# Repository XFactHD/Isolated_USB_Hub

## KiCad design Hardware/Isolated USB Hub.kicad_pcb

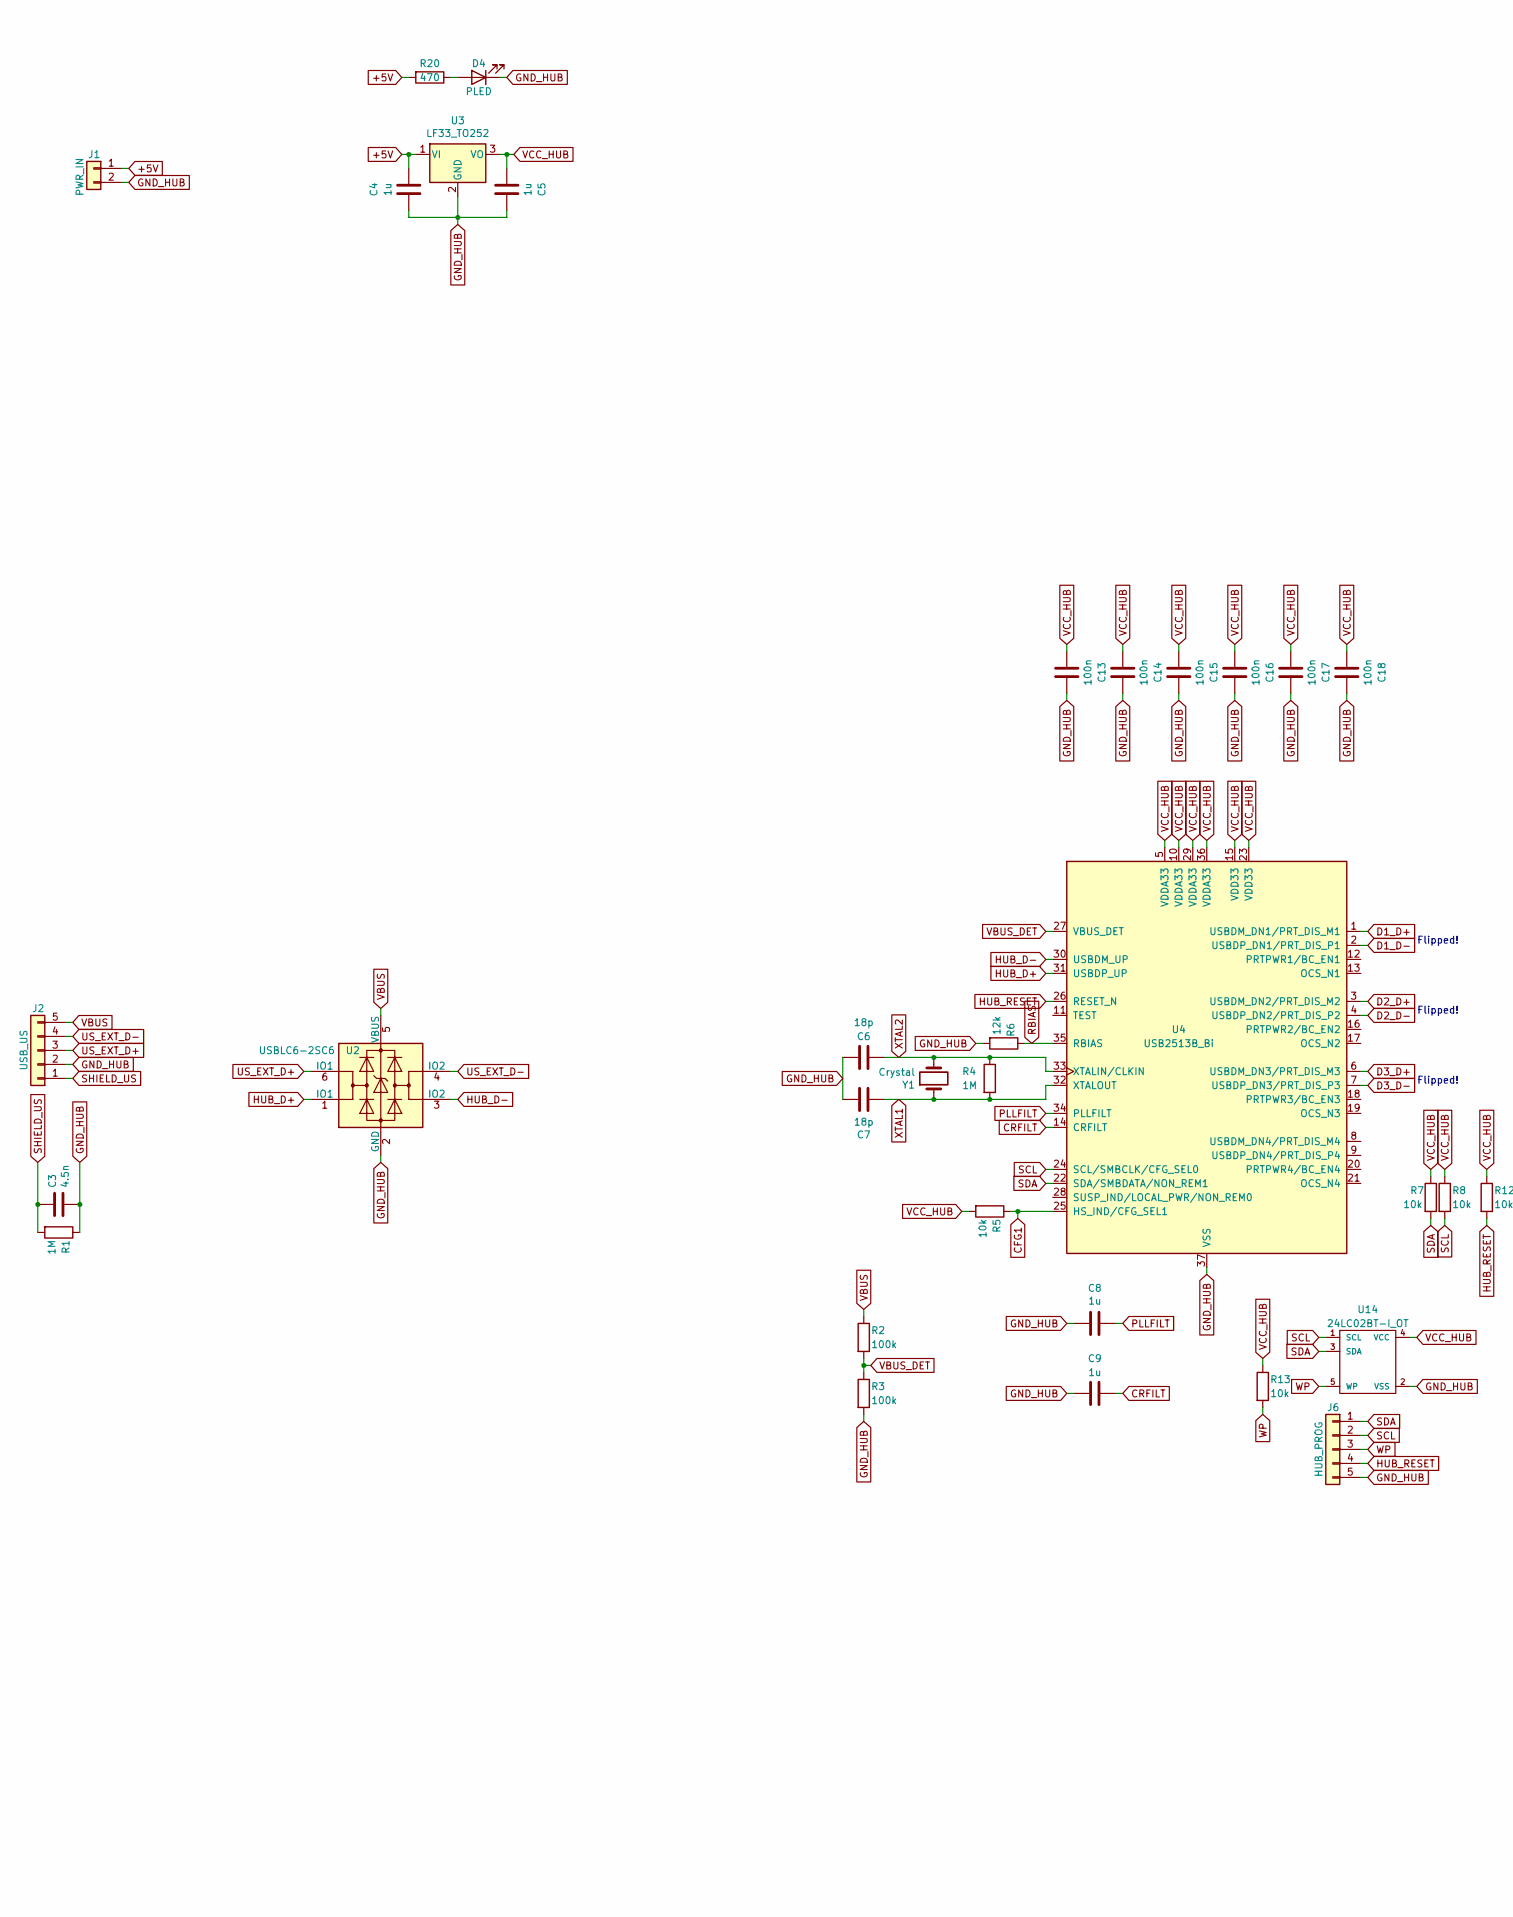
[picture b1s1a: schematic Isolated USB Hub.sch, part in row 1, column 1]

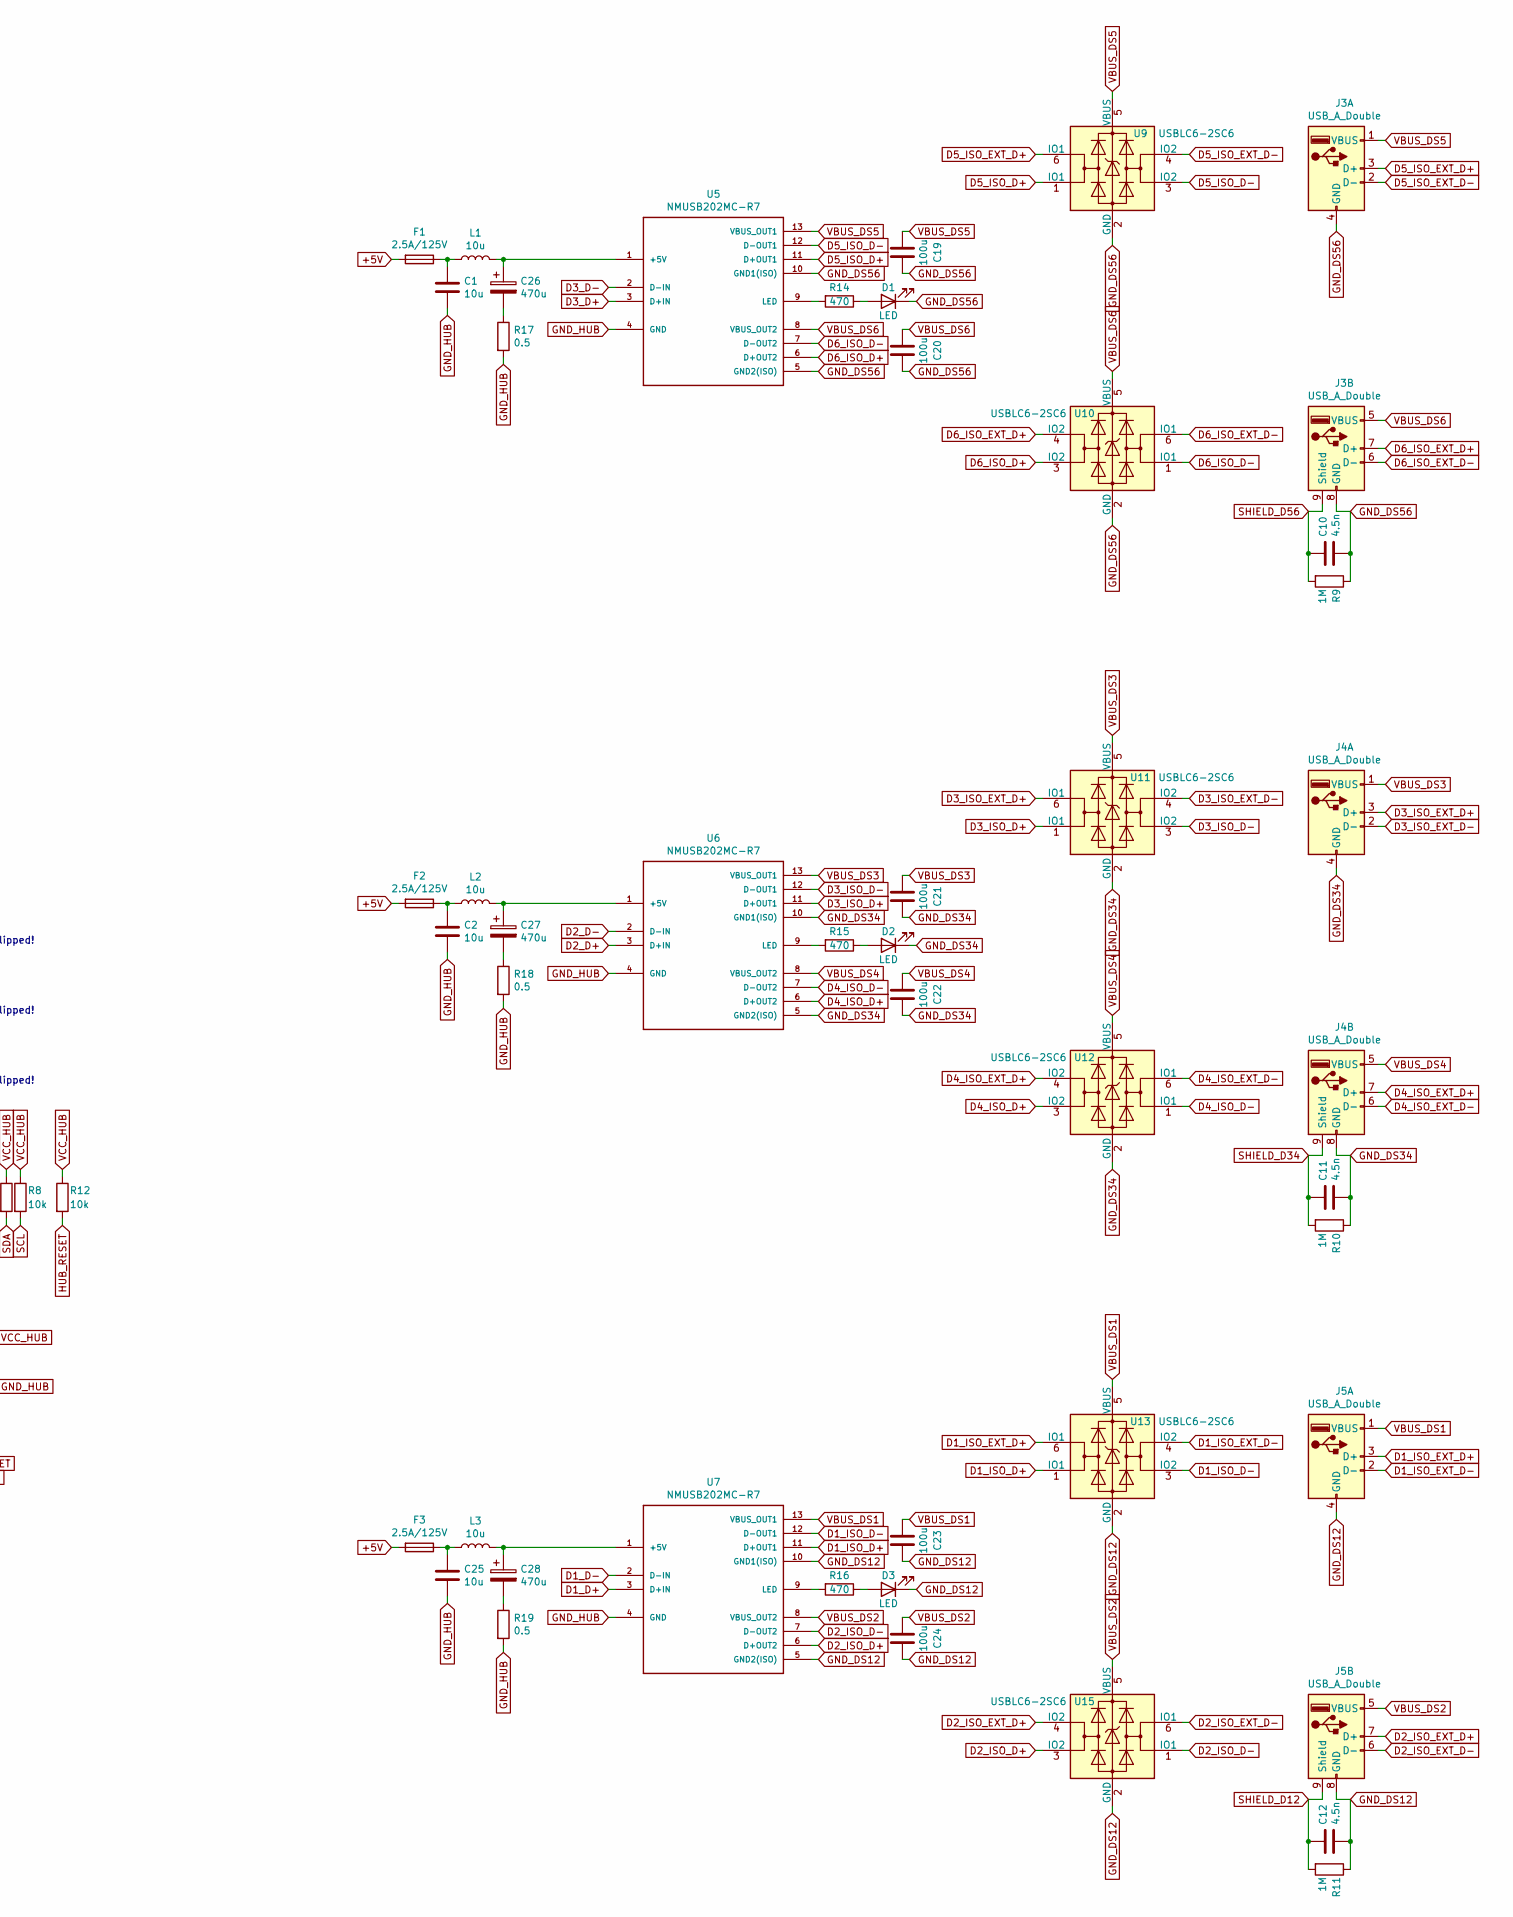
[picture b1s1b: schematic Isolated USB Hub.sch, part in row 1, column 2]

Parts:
C1, C2, C25: 10u; C_0805
C3, C10, C11, C12: 4.5n; C_0805
C4, C5, C8, C9: 1u; C_0805
C6, C7: 18p; C_0805
C13, C14, C15, C16, C17, C18: 100n; C_0805
C19, C20, C21, C22, C23, C24: 100u; C_0805
C26, C27, C28: 470u; CP_Tantalum_Case-B_EIA-3528-21_Reflow
D1, D2, D3: LED; Pin_Header_Straight_1x02_Pitch2.54mm
D4: PLED; Pin_Header_Straight_1x02_Pitch2.54mm
F1, F2, F3: 2.5A/125V; Fuse_SMD1206_Wave
J1: PWR_IN; PhoenixContact_MSTBA-G_02x5.08mm_Angled
J2: USB_US; Pin_Header_Angled_1x05_Pitch2.54mm
J3, J4, J5: USB_A_Double; USB-A-D-F-B-TH
J6: HUB_PROG; Pin_Header_Straight_1x05_Pitch1.27mm
L1, L2, L3: 10u; L_0805
R1, R4, R9, R10, R11: 1M; R_0805
R2, R3: 100k; R_0805
R5, R7, R8, R12, R13: 10k; R_0805
R6: 12k; R_0805
R14, R15, R16, R20: 470; R_0805
R17, R18, R19: 0.5; R_0805
U2, U9, U10, U11, U12, U13, U15: USBLC6-2SC6; SOT-23-6
U3: LF33_TO252; TO-252-2
U4: USB2513B_Bi; QFN-36-1EP_6x6mm_Pitch0.5mm
U5, U6, U7: NMUSB202MC-R7; IC_NMUSB202MC-R7
U14: 24LC02BT-I_OT; SOT-23-5
Y1: Crystal; Crystal_SMD_5032-2pin_5.0x3.2mm

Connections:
+5V: C4.1, F1.2, F2.2, F3.2, J1.1, R20.2, U3.1 (VI)
CFG1: R5.1, U4.25 (HS_IND/CFG_SEL1)
CRFILT: C9.1, U4.14 (CRFILT)
D1_D+: U4.1 (USBDM_DN1/PRT_DIS_M1), U7.3 (D+IN)
D1_D-: U4.2 (USBDP_DN1/PRT_DIS_P1), U7.2 (D-IN)
D1_ISO_D+: U7.11 (D+OUT1), U13.1 (IO1)
D1_ISO_D-: U7.12 (D-OUT1), U13.3 (IO2)
D1_ISO_EXT_D+: J5.3 (D+), U13.6 (IO1)
D1_ISO_EXT_D-: J5.2 (D-), U13.4 (IO2)
D2_D+: U4.3 (USBDM_DN2/PRT_DIS_M2), U6.3 (D+IN)
D2_D-: U4.4 (USBDP_DN2/PRT_DIS_P2), U6.2 (D-IN)
D2_ISO_D+: U7.6 (D+OUT2), U15.3 (IO2)
D2_ISO_D-: U7.7 (D-OUT2), U15.1 (IO1)
D2_ISO_EXT_D+: J5.7 (D+), U15.4 (IO2)
D2_ISO_EXT_D-: J5.6 (D-), U15.6 (IO1)
D3_D+: U4.6 (USBDM_DN3/PRT_DIS_M3), U5.3 (D+IN)
D3_D-: U4.7 (USBDP_DN3/PRT_DIS_P3), U5.2 (D-IN)
D3_ISO_D+: U6.11 (D+OUT1), U11.1 (IO1)
D3_ISO_D-: U6.12 (D-OUT1), U11.3 (IO2)
D3_ISO_EXT_D+: J4.3 (D+), U11.6 (IO1)
D3_ISO_EXT_D-: J4.2 (D-), U11.4 (IO2)
D4_ISO_D+: U6.6 (D+OUT2), U12.3 (IO2)
D4_ISO_D-: U6.7 (D-OUT2), U12.1 (IO1)
D4_ISO_EXT_D+: J4.7 (D+), U12.4 (IO2)
D4_ISO_EXT_D-: J4.6 (D-), U12.6 (IO1)
D5_ISO_D+: U5.11 (D+OUT1), U9.1 (IO1)
D5_ISO_D-: U5.12 (D-OUT1), U9.3 (IO2)
D5_ISO_EXT_D+: J3.3 (D+), U9.6 (IO1)
D5_ISO_EXT_D-: J3.2 (D-), U9.4 (IO2)
D6_ISO_D+: U5.6 (D+OUT2), U10.3 (IO2)
D6_ISO_D-: U5.7 (D-OUT2), U10.1 (IO1)
D6_ISO_EXT_D+: J3.7 (D+), U10.4 (IO2)
D6_ISO_EXT_D-: J3.6 (D-), U10.6 (IO1)
GND_DS12: C12.1, C23.1, C24.1, D3.1 (K), J5.4 (GND), J5.8 (GND), R11.1, U7.5 (GND2(ISO)), U7.10 (GND1(ISO)), U13.2 (GND), U15.2 (GND)
GND_DS34: C11.1, C21.1, C22.1, D2.1 (K), J4.4 (GND), J4.8 (GND), R10.1, U6.5 (GND2(ISO)), U6.10 (GND1(ISO)), U11.2 (GND), U12.2 (GND)
GND_DS56: C10.1, C19.1, C20.1, D1.1 (K), J3.4 (GND), J3.8 (GND), R9.1, U5.5 (GND2(ISO)), U5.10 (GND1(ISO)), U9.2 (GND), U10.2 (GND)
GND_HUB: C1.2, C2.2, C3.1, C4.2, C5.1, C6.1, C7.1, C8.2, C9.2, C13.1, C14.1, C15.1, C16.1, C17.1, C18.1, C25.2, D4.1 (K), J1.2, J2.2, J6.5, R1.1, R3.2, R6.2, R17.2, R18.2, R19.2, U2.2 (GND), U3.2 (GND), U4.37 (VSS), U5.4 (GND), U6.4 (GND), U7.4 (GND), U14.2 (VSS)
HUB_D+: U2.1 (IO1), U4.31 (USBDP_UP)
HUB_D-: U2.3 (IO2), U4.30 (USBDM_UP)
HUB_RESET: J6.4, R12.2, U4.26 (RESET_N)
unnamed: C1.1, F1.1, L1.1
unnamed: C2.1, F2.1, L2.1
unnamed: C25.1, F3.1, L3.1
unnamed: C26.1, L1.2, U5.1 (+5V)
unnamed: C26.2, R17.1
unnamed: C27.1, L2.2, U6.1 (+5V)
unnamed: C27.2, R18.1
unnamed: C28.1, L3.2, U7.1 (+5V)
unnamed: C28.2, R19.1
unnamed: D1.2 (A), R14.1
unnamed: D2.2 (A), R15.1
unnamed: D3.2 (A), R16.1
unnamed: D4.2 (A), R20.1
unnamed: R14.2, U5.9 (LED)
unnamed: R15.2, U6.9 (LED)
unnamed: R16.2, U7.9 (LED)
PLLFILT: C8.1, U4.34 (PLLFILT)
RBIAS: R6.1, U4.35 (RBIAS)
SCL: J6.2, R8.2, U4.24 (SCL/SMBCLK/CFG_SEL0), U14.1 (SCL)
SDA: J6.1, R7.2, U4.22 (SDA/SMBDATA/NON_REM1), U14.3 (SDA)
SHIELD_D12: C12.2, J5.9 (Shield), R11.2
SHIELD_D34: C11.2, J4.9 (Shield), R10.2
SHIELD_D56: C10.2, J3.9 (Shield), R9.2
SHIELD_US: C3.2, J2.1, R1.2
US_EXT_D+: J2.3, U2.6 (IO1)
US_EXT_D-: J2.4, U2.4 (IO2)
VBUS: J2.5, R2.1, U2.5 (VBUS)
VBUS_DET: R2.2, R3.1, U4.27 (VBUS_DET)
VBUS_DS1: C23.2, J5.1 (VBUS), U7.13 (VBUS_OUT1), U13.5 (VBUS)
VBUS_DS2: C24.2, J5.5 (VBUS), U7.8 (VBUS_OUT2), U15.5 (VBUS)
VBUS_DS3: C21.2, J4.1 (VBUS), U6.13 (VBUS_OUT1), U11.5 (VBUS)
VBUS_DS4: C22.2, J4.5 (VBUS), U6.8 (VBUS_OUT2), U12.5 (VBUS)
VBUS_DS5: C19.2, J3.1 (VBUS), U5.13 (VBUS_OUT1), U9.5 (VBUS)
VBUS_DS6: C20.2, J3.5 (VBUS), U5.8 (VBUS_OUT2), U10.5 (VBUS)
VCC_HUB: C5.2, C13.2, C14.2, C15.2, C16.2, C17.2, C18.2, R5.2, R7.1, R8.1, R12.1, R13.1, U3.3 (VO), U4.5 (VDDA33), U4.10 (VDDA33), U4.15 (VDD33), U4.23 (VDD33), U4.29 (VDDA33), U4.36 (VDDA33), U14.4 (VCC)
WP: J6.3, R13.2, U14.5 (WP)
XTAL1: C7.2, R4.2, U4.32 (XTALOUT), Y1.1
XTAL2: C6.2, R4.1, U4.33 (XTALIN/CLKIN), Y1.2

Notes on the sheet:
Flipped!

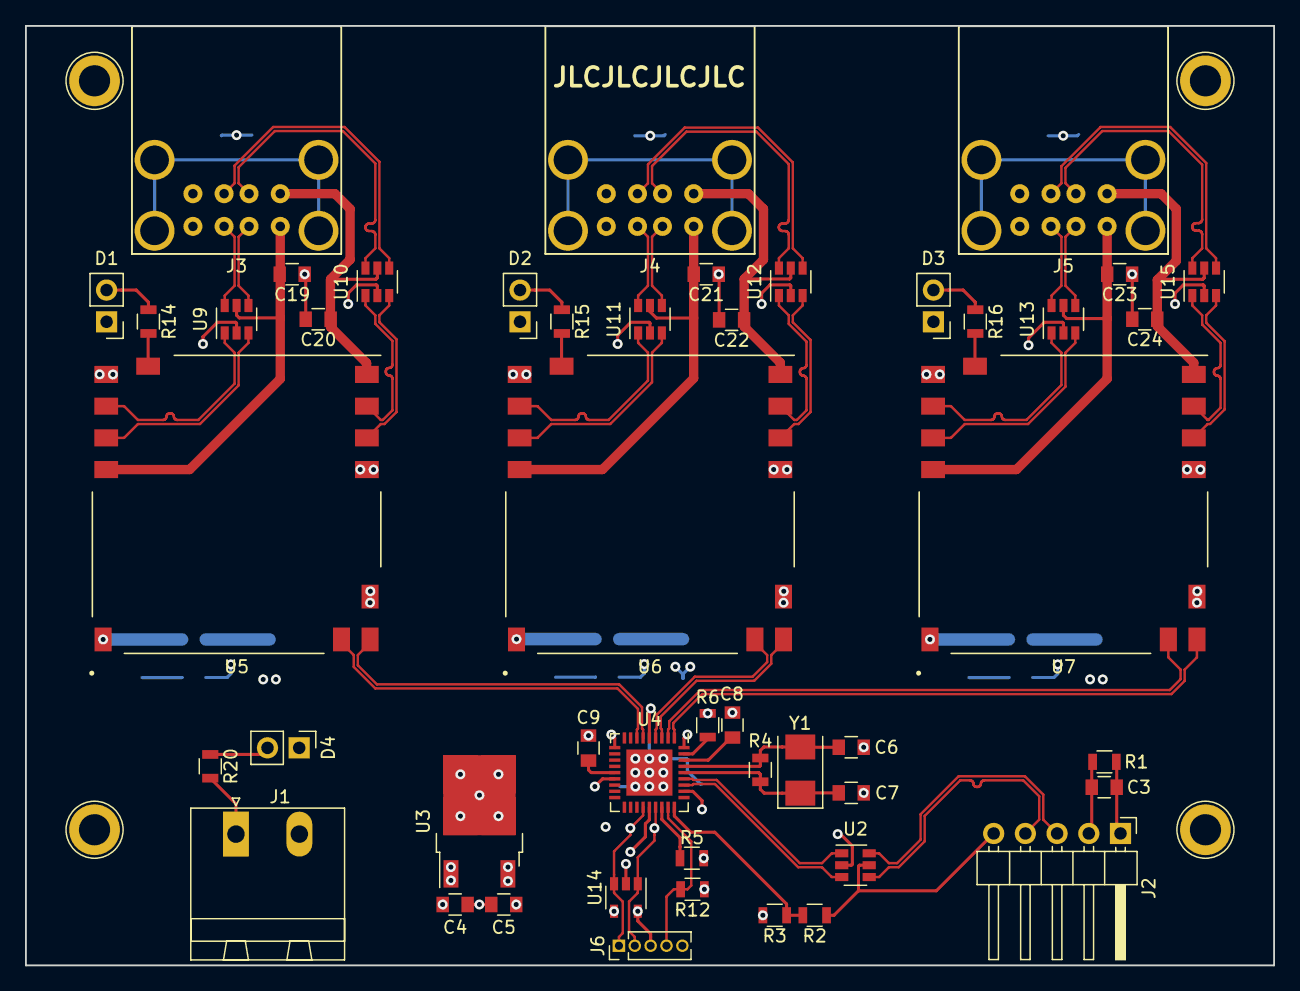
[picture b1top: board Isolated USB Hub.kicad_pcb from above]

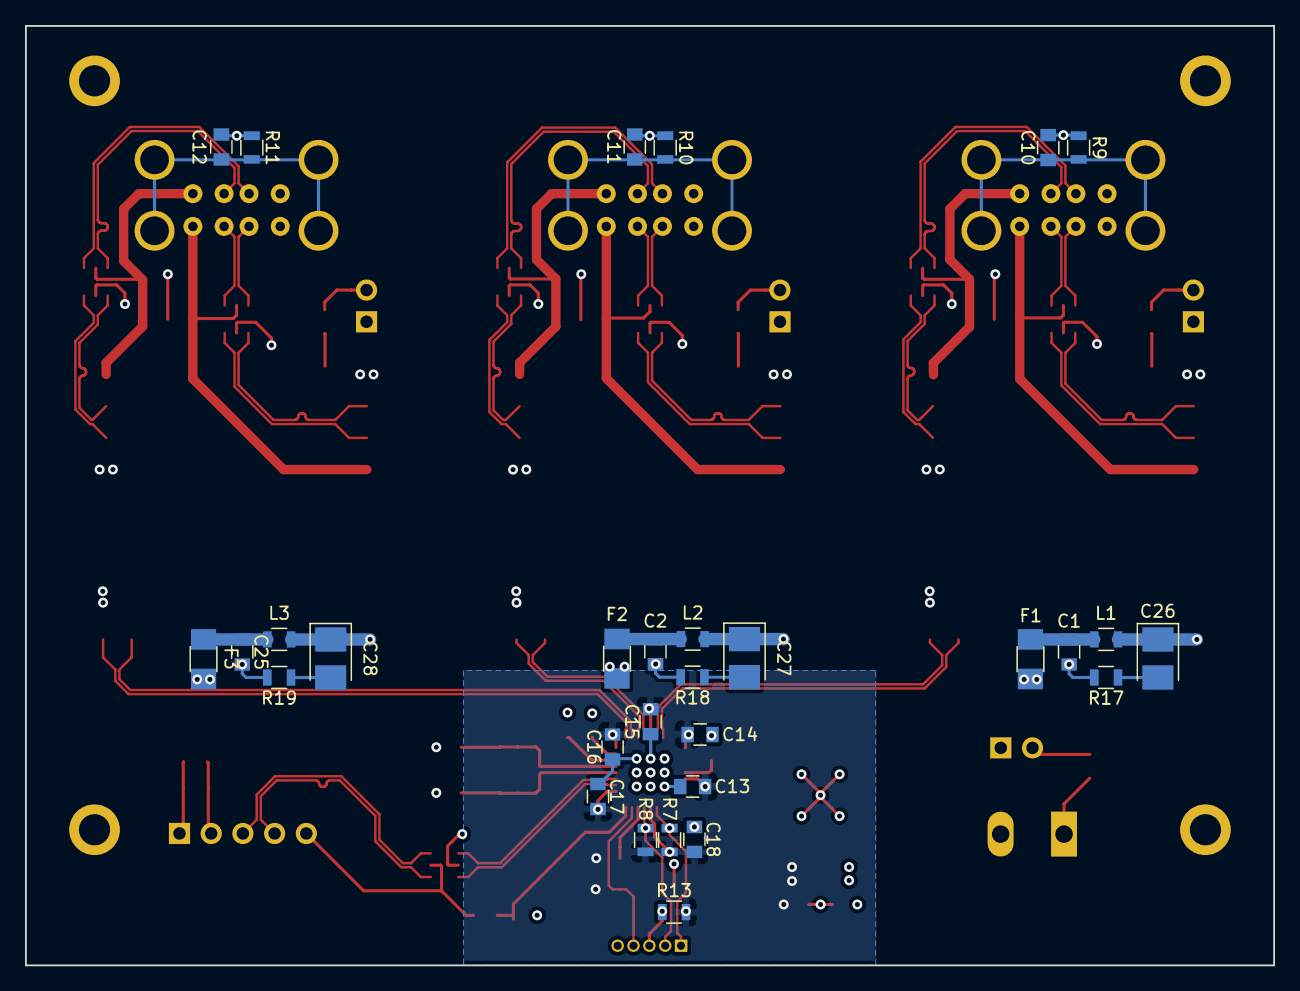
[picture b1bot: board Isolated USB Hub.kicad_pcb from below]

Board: 4 copper layers, 100.0 x 75.3 mm, 78 parts (30 on the bottom side), 78 nets.

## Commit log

2021-03-05 Add power LED
2021-11-19 Finish USB Panelmount
